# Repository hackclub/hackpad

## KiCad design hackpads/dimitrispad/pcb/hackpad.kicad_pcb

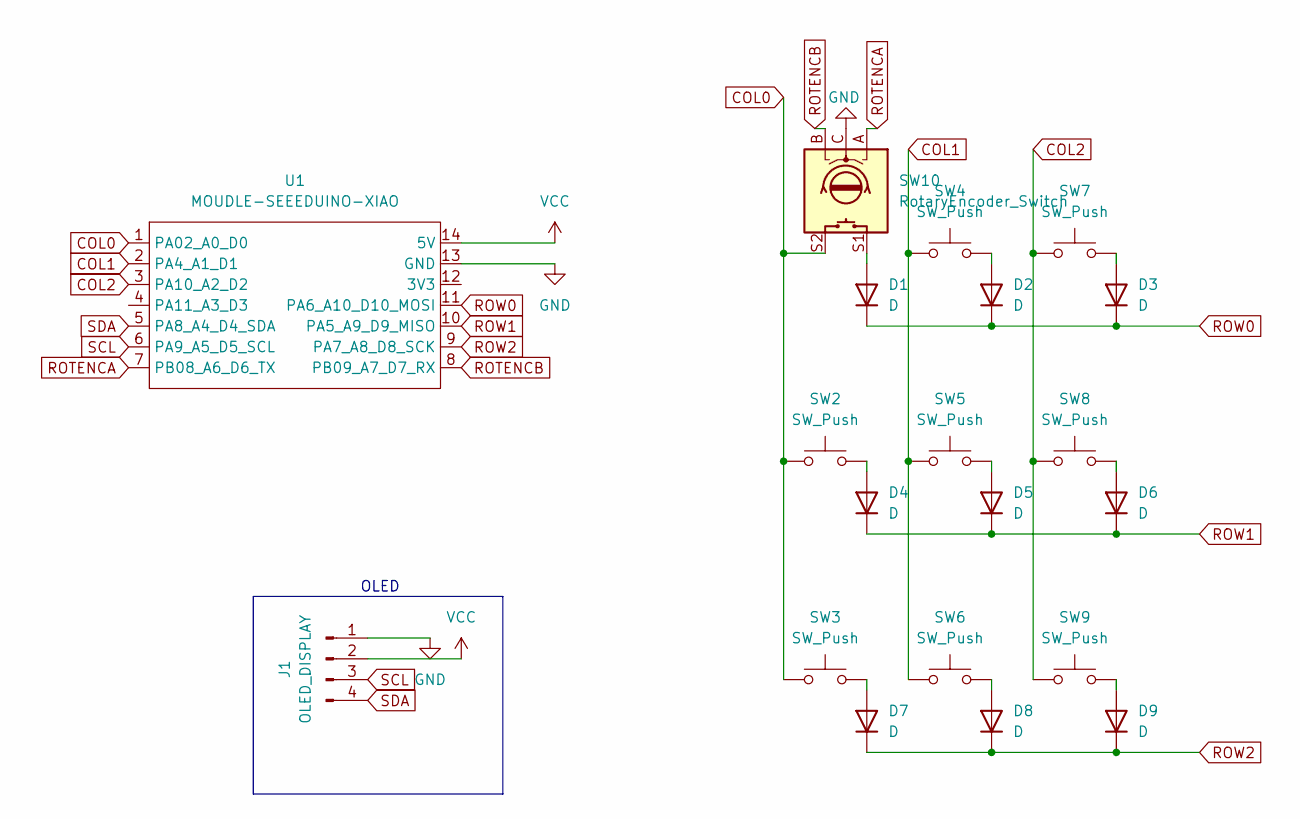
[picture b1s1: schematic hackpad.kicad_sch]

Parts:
D1, D2, D3, D4, D5, D6, D7, D8, D9: D; D_DO-35_SOD27_P7.62mm_Horizontal
J1: OLED_DISPLAY; SSD1306-0.91-OLED-4pin-128x32
SW2, SW3, SW4, SW5, SW6, SW7, SW8, SW9: SW_Push; SW_Cherry_MX_1.00u_PCB
SW10: RotaryEncoder_Switch; RotaryEncoder_Alps_EC11E-Switch_Vertical_H20mm
U1: MOUDLE-SEEEDUINO-XIAO; XIAO-Generic-Hybrid-14P-2.54-21X17.8MM

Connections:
COL0: SW2.1, SW3.1, SW10.S2, U1.1 (PA02_A0_D0)
COL1: SW4.1, SW5.1, SW6.1, U1.2 (PA4_A1_D1)
COL2: SW7.1, SW8.1, SW9.1, U1.3 (PA10_A2_D2)
GND: J1.1, SW10.C, U1.13 (GND)
unnamed: D1.2 (A), SW10.S1
unnamed: D2.2 (A), SW4.2
unnamed: D3.2 (A), SW7.2
unnamed: D4.2 (A), SW2.2
unnamed: D5.2 (A), SW5.2
unnamed: D6.2 (A), SW8.2
unnamed: D7.2 (A), SW3.2
unnamed: D8.2 (A), SW6.2
unnamed: D9.2 (A), SW9.2
ROTENCA: SW10.A, U1.7 (PB08_A6_D6_TX)
ROTENCB: SW10.B, U1.8 (PB09_A7_D7_RX)
ROW0: D1.1 (K), D2.1 (K), D3.1 (K), U1.11 (PA6_A10_D10_MOSI)
ROW1: D4.1 (K), D5.1 (K), D6.1 (K), U1.10 (PA5_A9_D9_MISO)
ROW2: D7.1 (K), D8.1 (K), D9.1 (K), U1.9 (PA7_A8_D8_SCK)
SCL: J1.3, U1.6 (PA9_A5_D5_SCL)
SDA: J1.4, U1.5 (PA8_A4_D4_SDA)
VCC: J1.2, U1.14 (5V)

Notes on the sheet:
OLED

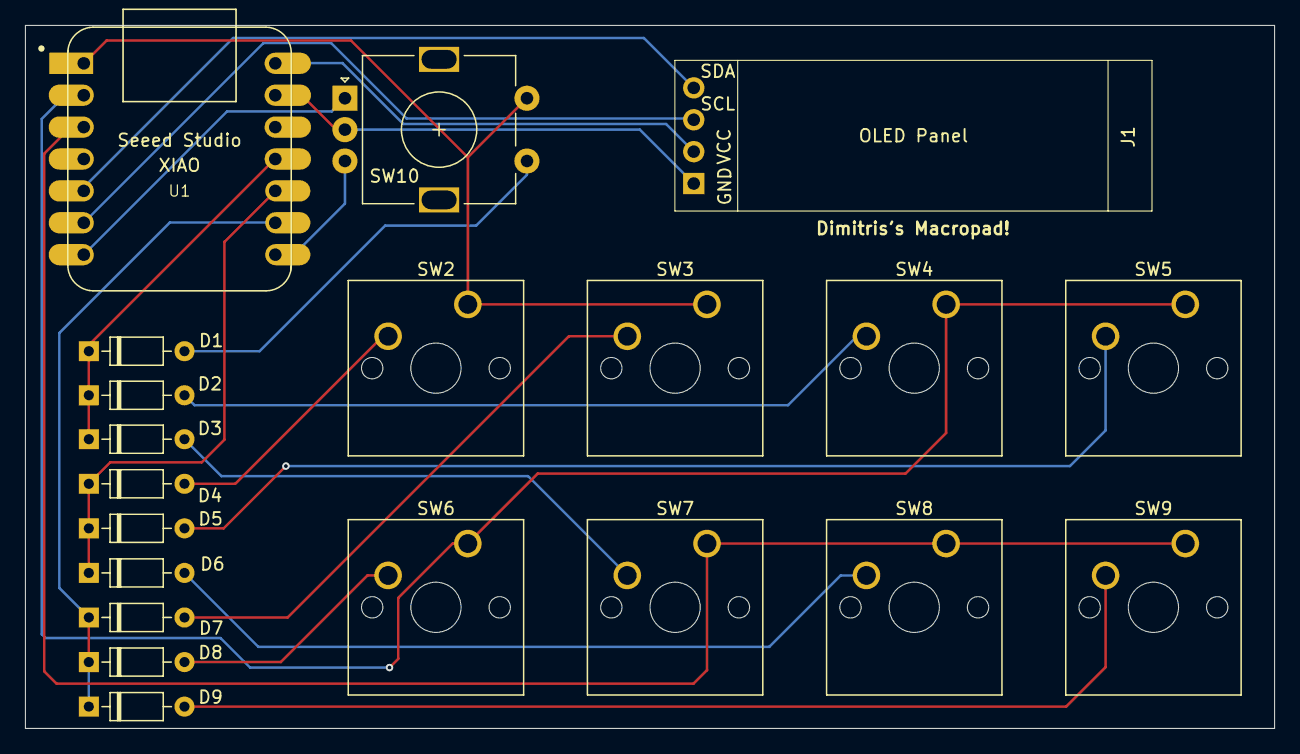
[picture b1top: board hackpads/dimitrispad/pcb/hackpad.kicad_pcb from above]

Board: 2 copper layers, 99.5 x 56.0 mm, 20 parts (0 on the bottom side), 21 nets.

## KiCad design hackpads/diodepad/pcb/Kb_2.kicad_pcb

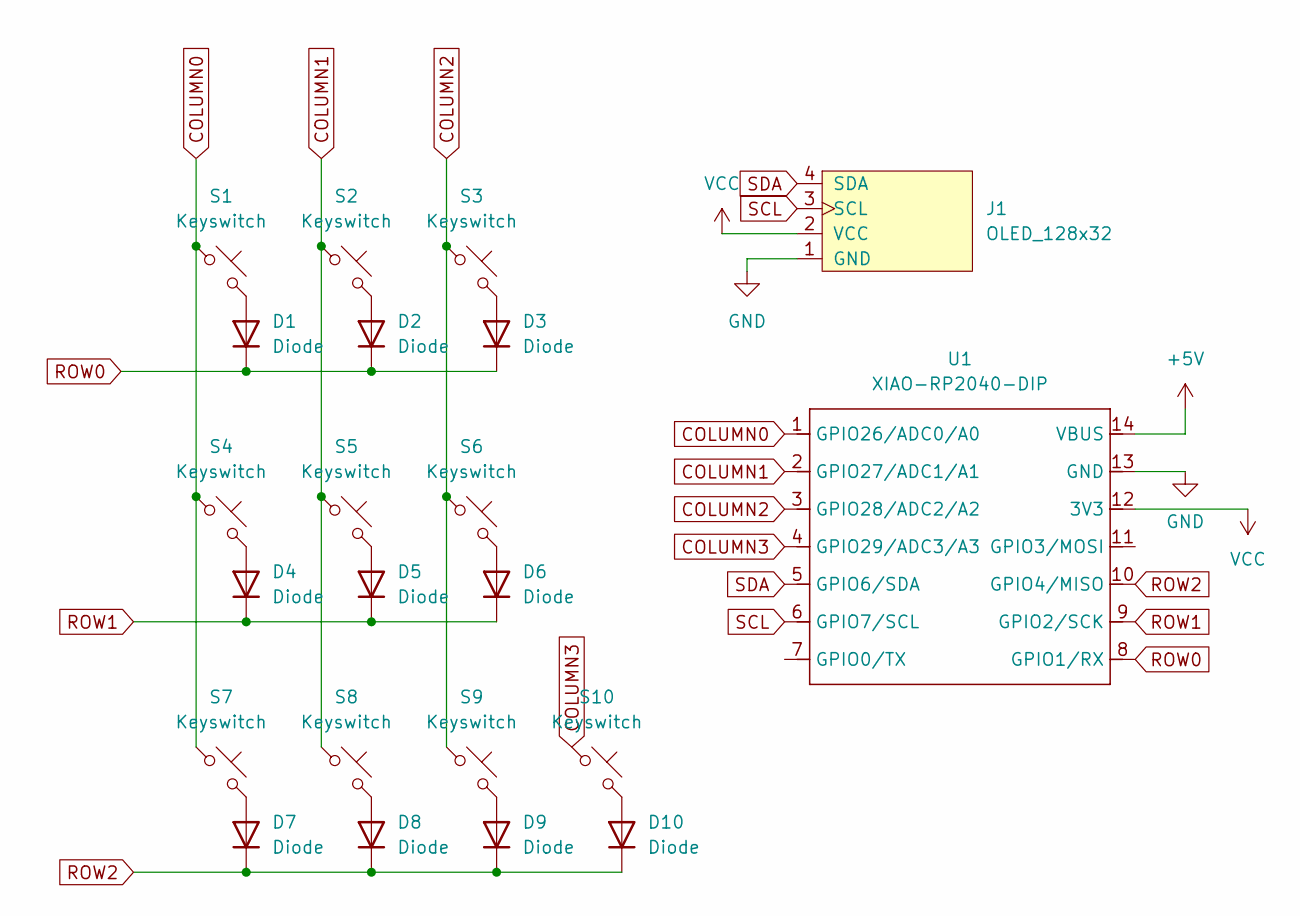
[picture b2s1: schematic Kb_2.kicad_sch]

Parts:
D1, D2, D3, D4, D5, D6, D7, D8, D9, D10: Diode; Diode_DO-35
J1: OLED_128x32
S1, S2, S3, S4, S5, S6, S7, S8, S9, S10: Keyswitch; MX_PCB_1.00u
U1: XIAO-RP2040-DIP

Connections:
+5V: U1.14 (VBUS)
COLUMN0: S1.1, S4.1, S7.1, U1.1 (GPIO26/ADC0/A0)
COLUMN1: S2.1, S5.1, S8.1, U1.2 (GPIO27/ADC1/A1)
COLUMN2: S3.1, S6.1, S9.1, U1.3 (GPIO28/ADC2/A2)
COLUMN3: S10.1, U1.4 (GPIO29/ADC3/A3)
GND: J1.1 (GND), U1.13 (GND)
unnamed: D1.2 (A), S1.2
unnamed: D2.2 (A), S2.2
unnamed: D3.2 (A), S3.2
unnamed: D4.2 (A), S4.2
unnamed: D5.2 (A), S5.2
unnamed: D6.2 (A), S6.2
unnamed: D7.2 (A), S7.2
unnamed: D8.2 (A), S8.2
unnamed: D9.2 (A), S9.2
unnamed: D10.2 (A), S10.2
ROW0: D1.1 (K), D2.1 (K), D3.1 (K), U1.8 (GPIO1/RX)
ROW1: D4.1 (K), D5.1 (K), D6.1 (K), U1.9 (GPIO2/SCK)
ROW2: D7.1 (K), D8.1 (K), D9.1 (K), D10.1 (K), U1.10 (GPIO4/MISO)
SCL: J1.3 (SCL), U1.6 (GPIO7/SCL)
SDA: J1.4 (SDA), U1.5 (GPIO6/SDA)
VCC: J1.2 (VCC), U1.12 (3V3)

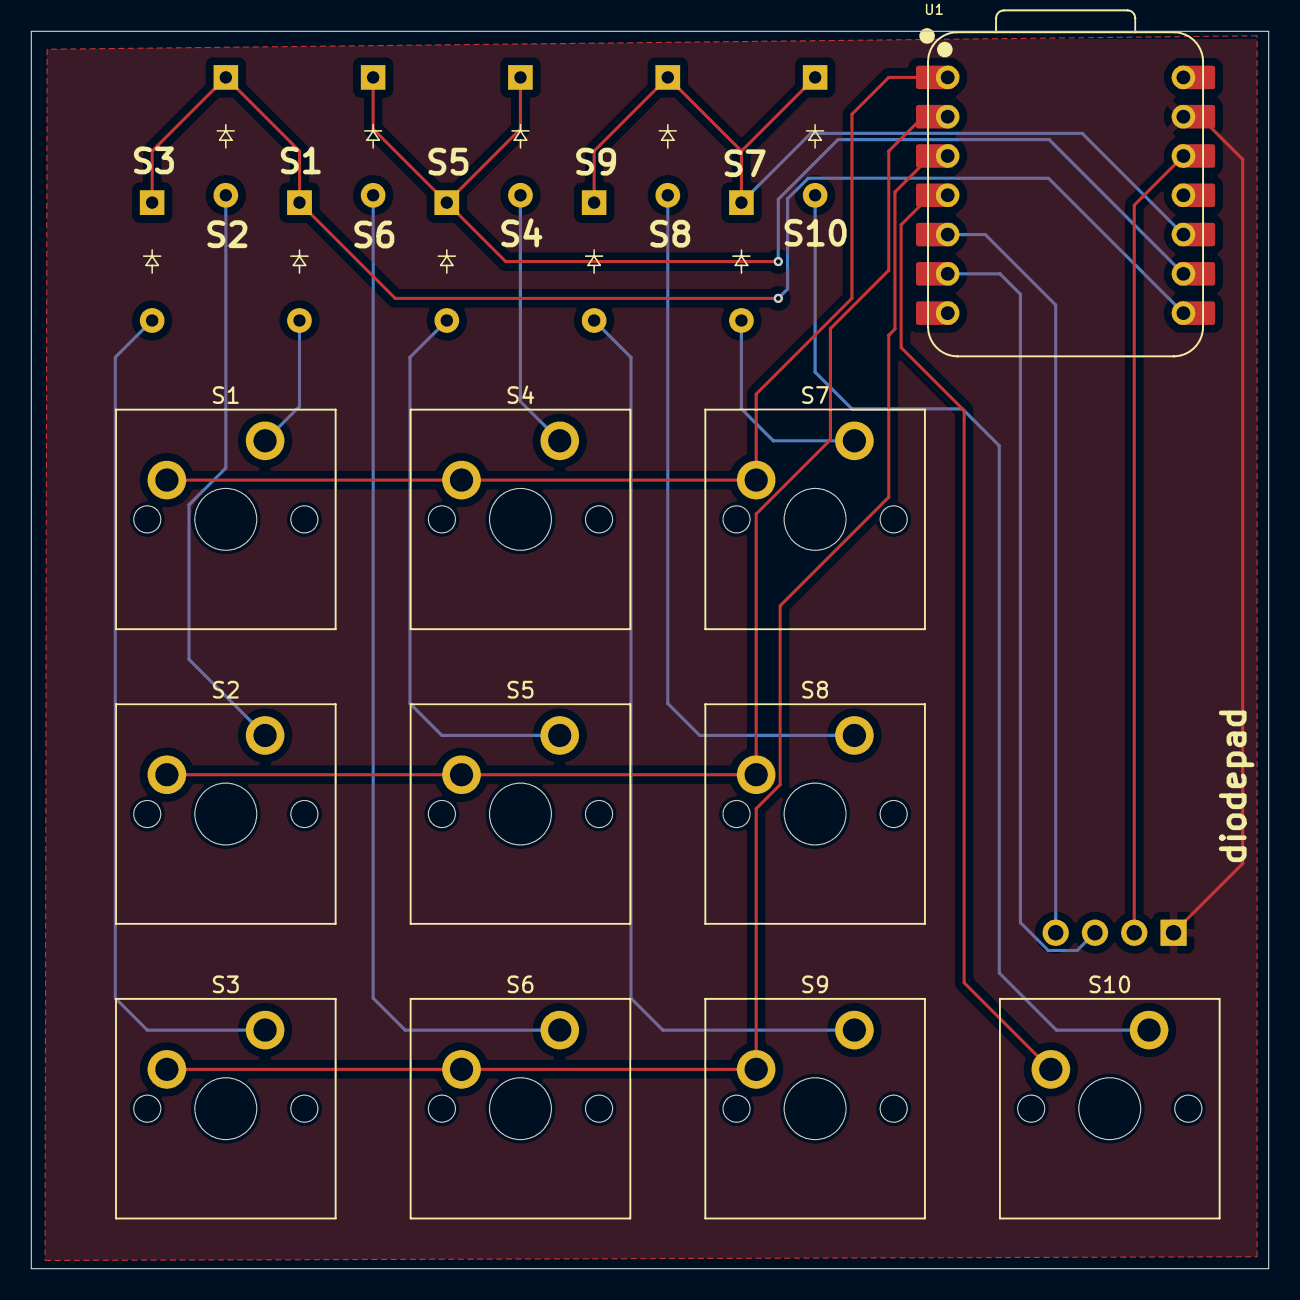
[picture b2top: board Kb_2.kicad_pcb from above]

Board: 2 copper layers, 80.0 x 80.0 mm, 22 parts (0 on the bottom side), 21 nets.

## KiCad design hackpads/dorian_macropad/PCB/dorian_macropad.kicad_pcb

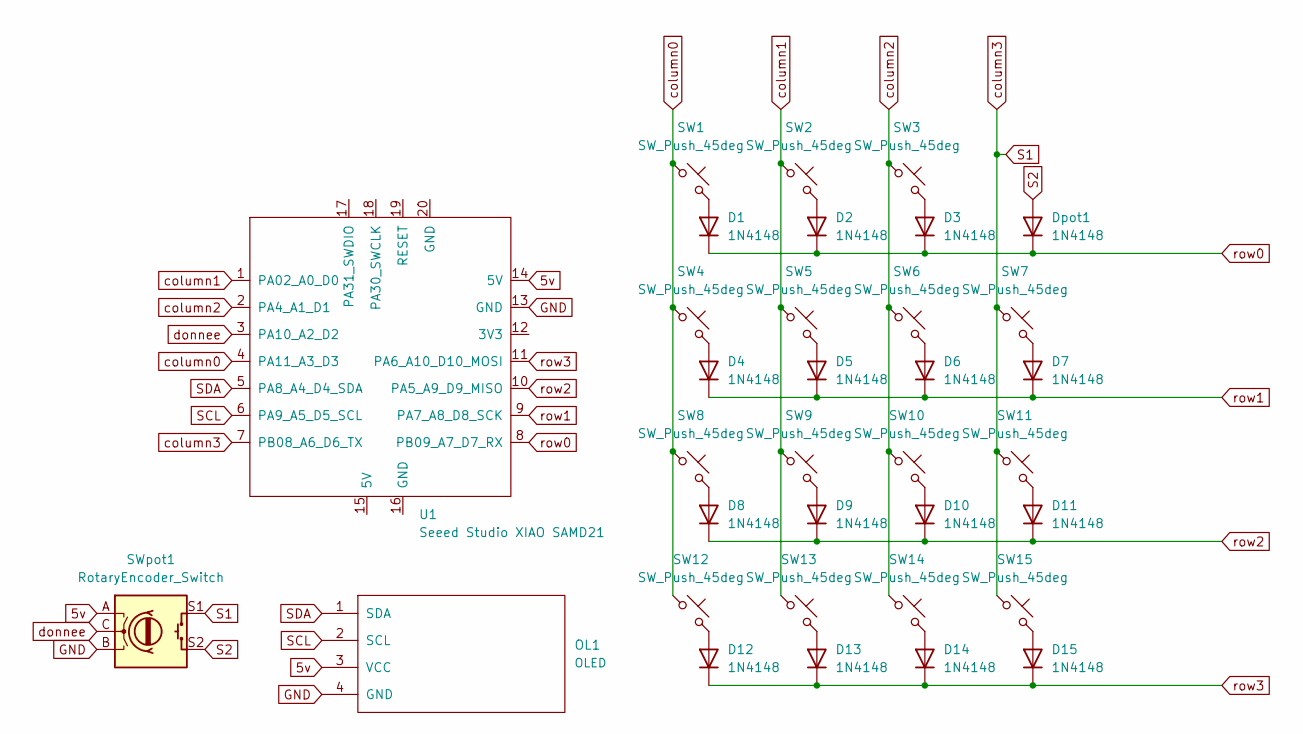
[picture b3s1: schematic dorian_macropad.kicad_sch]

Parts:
D1, D2, D3, D4, D5, D6, D7, D8, D9, D10, D11, D12, D13, D14, D15: 1N4148; D_DO-35_SOD27_P7.62mm_Horizontal
Dpot1: 1N4148; D_DO-35_SOD27_P7.62mm_Horizontal
OL1: OLED; 128x64OLED
SW1, SW2, SW3, SW4, SW5, SW6, SW7, SW8, SW9, SW10, SW11, SW12, SW13, SW14, SW15: SW_Push_45deg; SW_Cherry_MX_1.00u_PCB
SWpot1: RotaryEncoder_Switch; RotaryEncoder_Alps_EC11E-Switch_Vertical_H20mm
U1: Seeed Studio XIAO SAMD21; XIAO-SAMD21-DIP

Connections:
5v: OL1.3 (VCC), SWpot1.A, U1.14 (5V)
GND: OL1.4 (GND), SWpot1.B, U1.13 (GND)
unnamed: D1.2 (A), SW1.2
unnamed: D2.2 (A), SW2.2
unnamed: D3.2 (A), SW3.2
unnamed: D4.2 (A), SW4.2
unnamed: D5.2 (A), SW5.2
unnamed: D6.2 (A), SW6.2
unnamed: D7.2 (A), SW7.2
unnamed: D8.2 (A), SW8.2
unnamed: D9.2 (A), SW9.2
unnamed: D10.2 (A), SW10.2
unnamed: D11.2 (A), SW11.2
unnamed: D12.2 (A), SW12.2
unnamed: D13.2 (A), SW13.2
unnamed: D14.2 (A), SW14.2
unnamed: D15.2 (A), SW15.2
S1: SW7.1, SW11.1, SW15.1, SWpot1.S1, U1.7 (PB08_A6_D6_TX)
S2: Dpot1.2 (A), SWpot1.S2
SCL: OL1.2 (SCL), U1.6 (PA9_A5_D5_SCL)
SDA: OL1.1 (SDA), U1.5 (PA8_A4_D4_SDA)
column0: SW1.1, SW4.1, SW8.1, SW12.1, U1.4 (PA11_A3_D3)
column1: SW2.1, SW5.1, SW9.1, SW13.1, U1.1 (PA02_A0_D0)
column2: SW3.1, SW6.1, SW10.1, SW14.1, U1.2 (PA4_A1_D1)
donnee: SWpot1.C, U1.3 (PA10_A2_D2)
row0: D1.1 (K), D2.1 (K), D3.1 (K), Dpot1.1 (K), U1.8 (PB09_A7_D7_RX)
row1: D4.1 (K), D5.1 (K), D6.1 (K), D7.1 (K), U1.9 (PA7_A8_D8_SCK)
row2: D8.1 (K), D9.1 (K), D10.1 (K), D11.1 (K), U1.10 (PA5_A9_D9_MISO)
row3: D12.1 (K), D13.1 (K), D14.1 (K), D15.1 (K), U1.11 (PA6_A10_D10_MOSI)

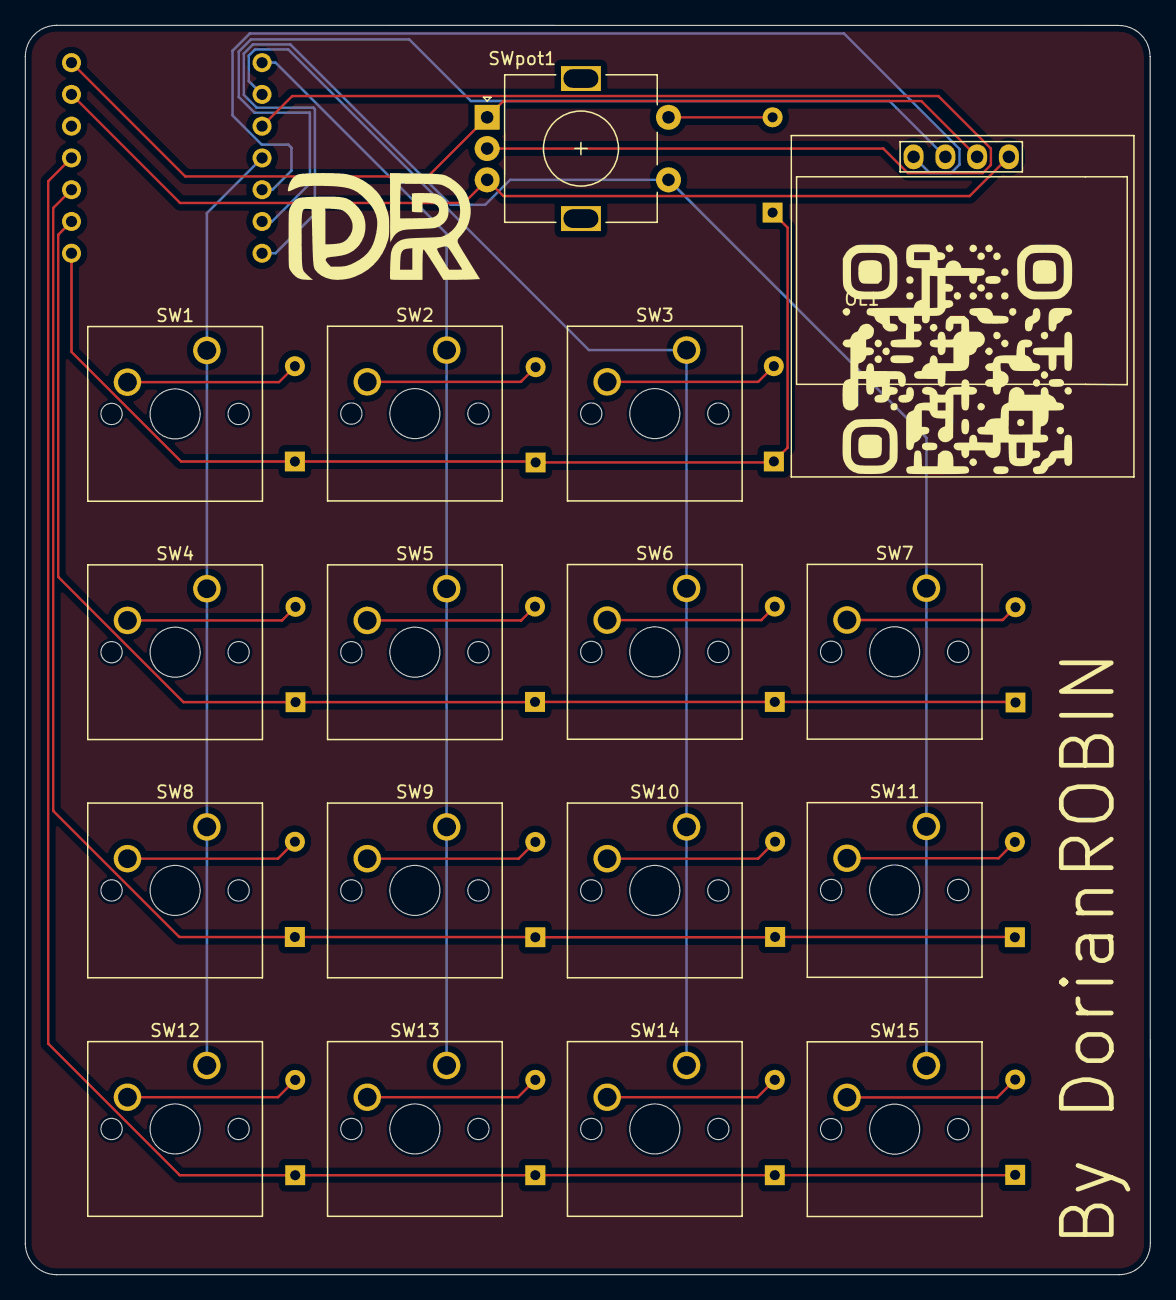
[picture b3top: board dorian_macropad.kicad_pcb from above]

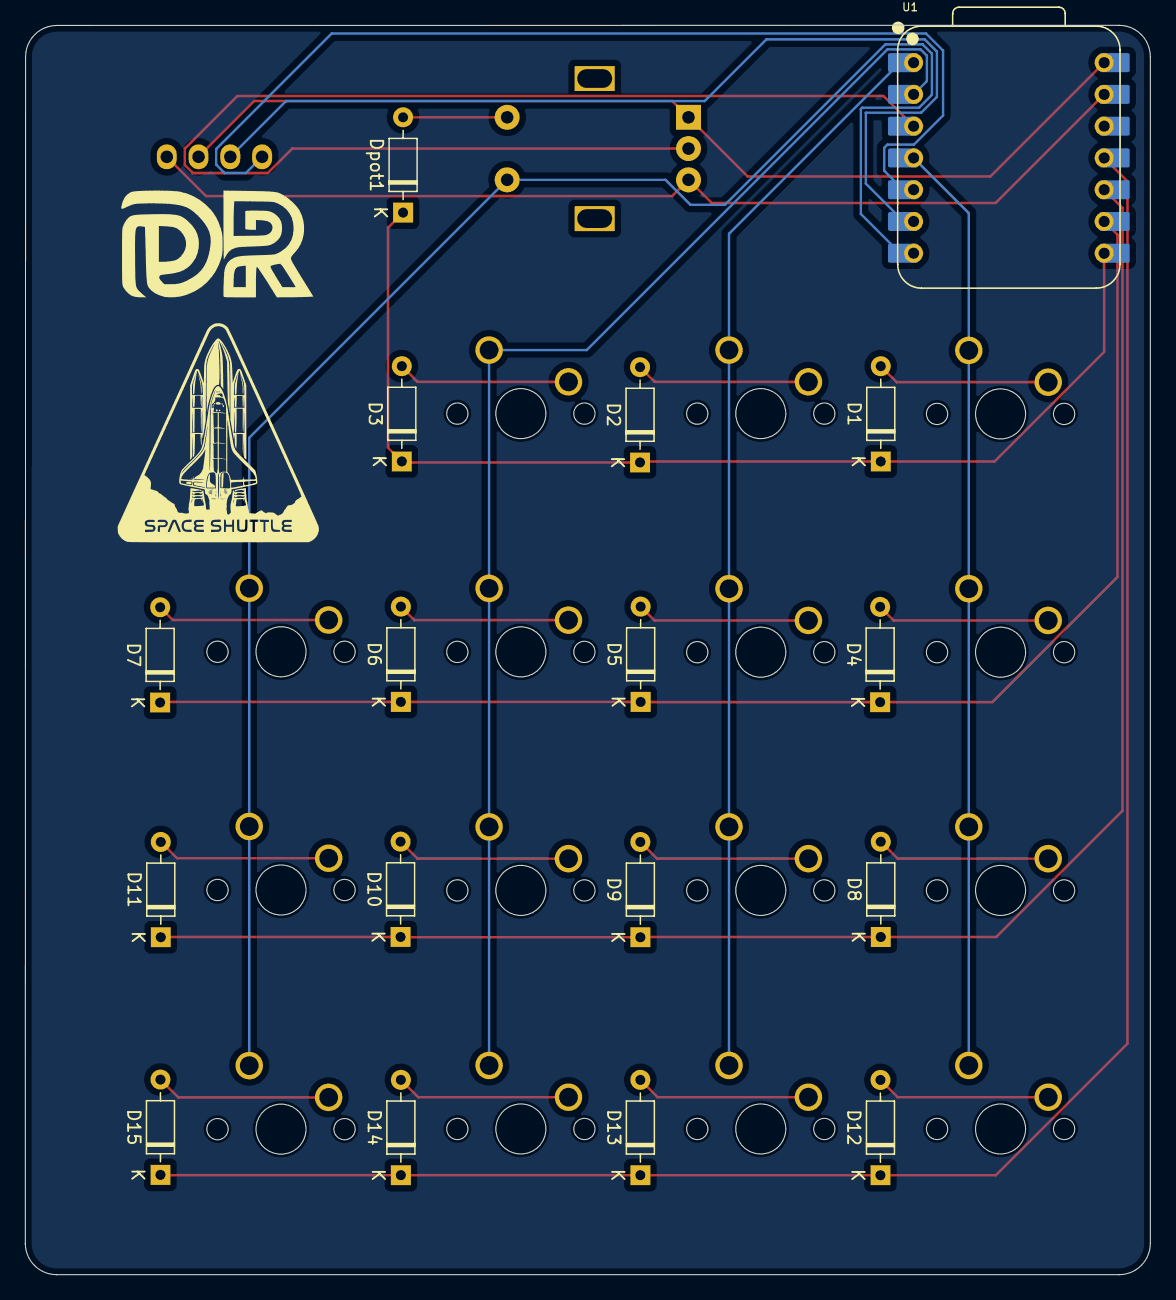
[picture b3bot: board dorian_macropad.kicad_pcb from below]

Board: 2 copper layers, 90.0 x 99.9 mm, 34 parts (17 on the bottom side), 29 nets.

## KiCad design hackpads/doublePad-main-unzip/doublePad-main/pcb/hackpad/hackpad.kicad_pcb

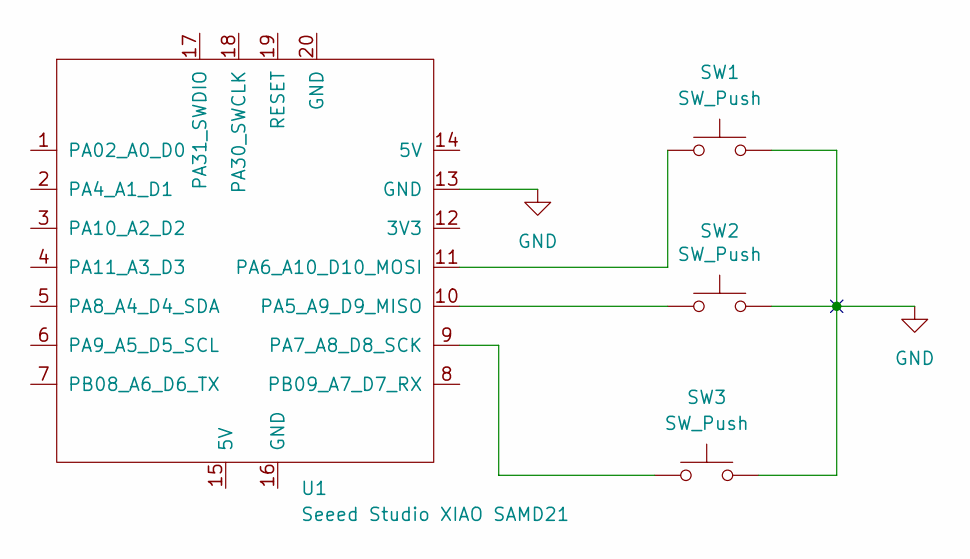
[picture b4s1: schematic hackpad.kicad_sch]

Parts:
SW1, SW2, SW3: SW_Push; SW_Cherry_MX_1.00u_PCB
U1: Seeed Studio XIAO SAMD21; XIAO-Generic-Thruhole-14P-2.54-21X17.8MM

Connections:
GND: SW1.2, SW2.2, SW3.2, U1.13 (GND)
unnamed: SW2.1, U1.10 (PA5_A9_D9_MISO)
unnamed: SW1.1, U1.11 (PA6_A10_D10_MOSI)
unnamed: SW3.1, U1.9 (PA7_A8_D8_SCK)

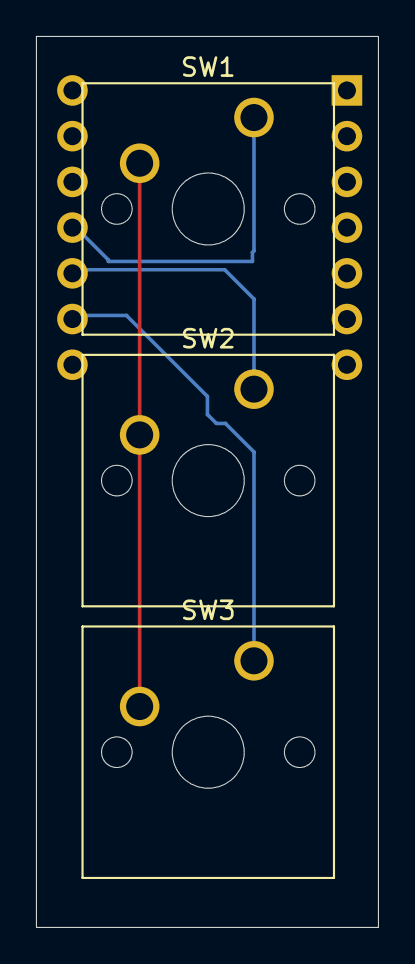
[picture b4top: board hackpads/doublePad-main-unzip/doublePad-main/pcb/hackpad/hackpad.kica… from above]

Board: 2 copper layers, 19.0 x 49.5 mm, 4 parts (1 on the bottom side), 4 nets.

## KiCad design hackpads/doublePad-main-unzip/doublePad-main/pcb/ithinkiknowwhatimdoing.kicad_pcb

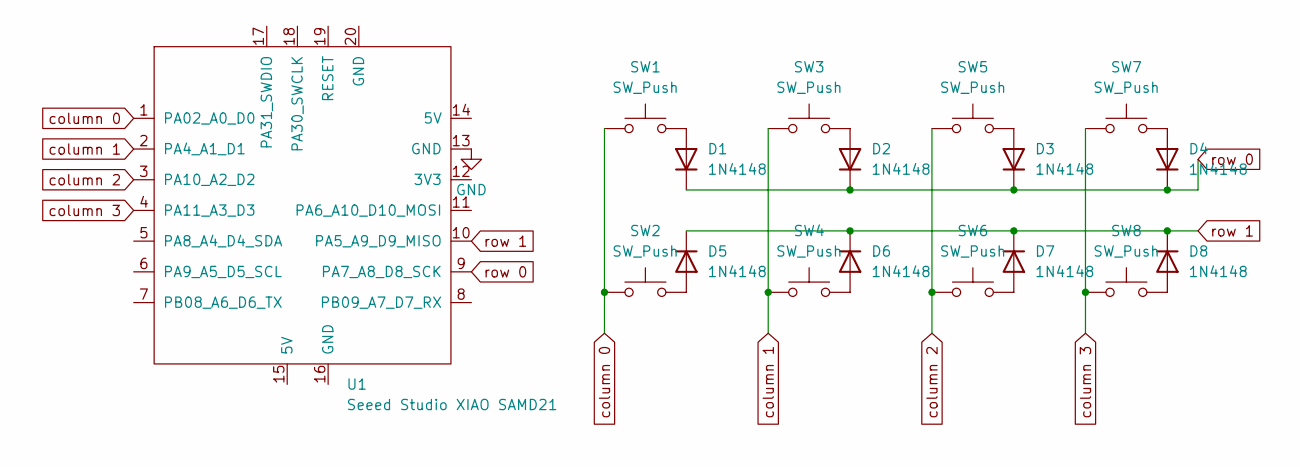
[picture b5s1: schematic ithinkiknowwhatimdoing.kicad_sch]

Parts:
D1, D2, D3, D4, D5, D6, D7, D8: 1N4148; D_DO-35_SOD27_P7.62mm_Horizontal
SW1, SW2, SW3, SW4, SW5, SW6, SW7, SW8: SW_Push; SW_Cherry_MX_1.00u_Plate
U1: Seeed Studio XIAO SAMD21; XIAO-Generic-Thruhole-14P-2.54-21X17.8MM

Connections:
GND: U1.13 (GND)
unnamed: D1.2 (A), SW1.2
unnamed: D2.2 (A), SW3.2
unnamed: D3.2 (A), SW5.2
unnamed: D4.2 (A), SW7.2
unnamed: D5.2 (A), SW2.2
unnamed: D6.2 (A), SW4.2
unnamed: D7.2 (A), SW6.2
unnamed: D8.2 (A), SW8.2
column 0: SW1.1, SW2.1, U1.1 (PA02_A0_D0)
column 1: SW3.1, SW4.1, U1.2 (PA4_A1_D1)
column 2: SW5.1, SW6.1, U1.3 (PA10_A2_D2)
column 3: SW7.1, SW8.1, U1.4 (PA11_A3_D3)
row 0: D1.1 (K), D2.1 (K), D3.1 (K), D4.1 (K), U1.9 (PA7_A8_D8_SCK)
row 1: D5.1 (K), D6.1 (K), D7.1 (K), D8.1 (K), U1.10 (PA5_A9_D9_MISO)

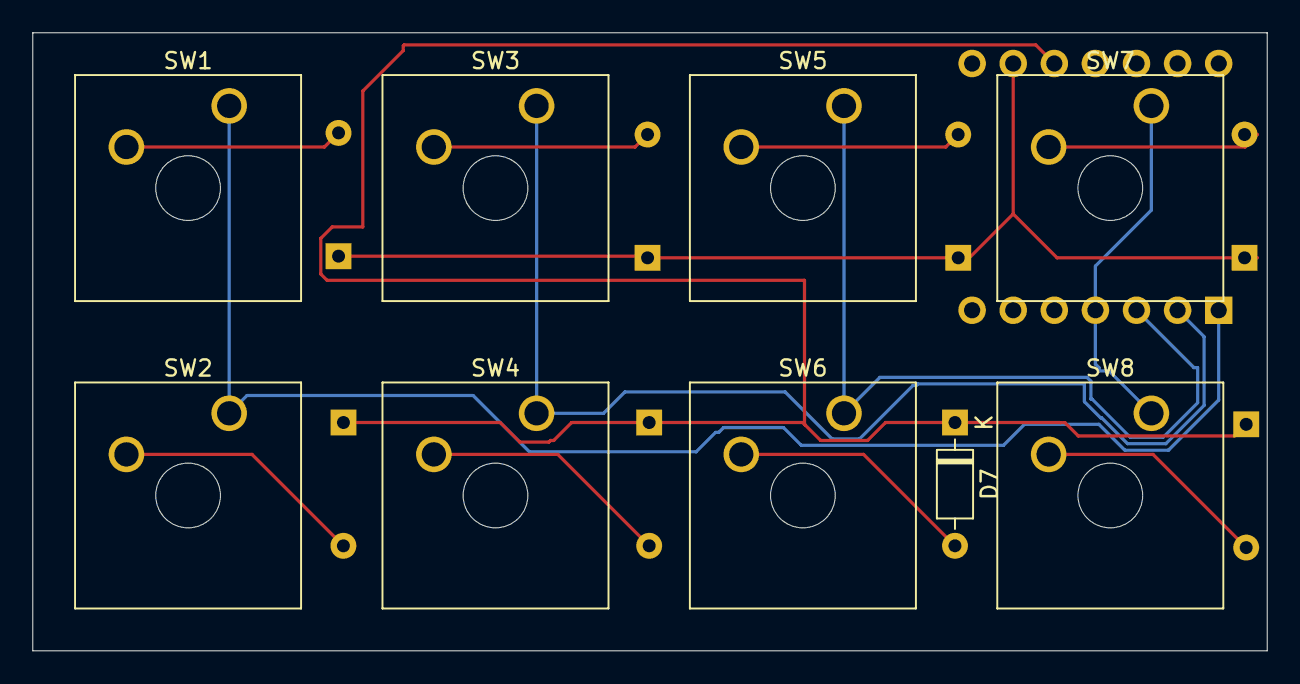
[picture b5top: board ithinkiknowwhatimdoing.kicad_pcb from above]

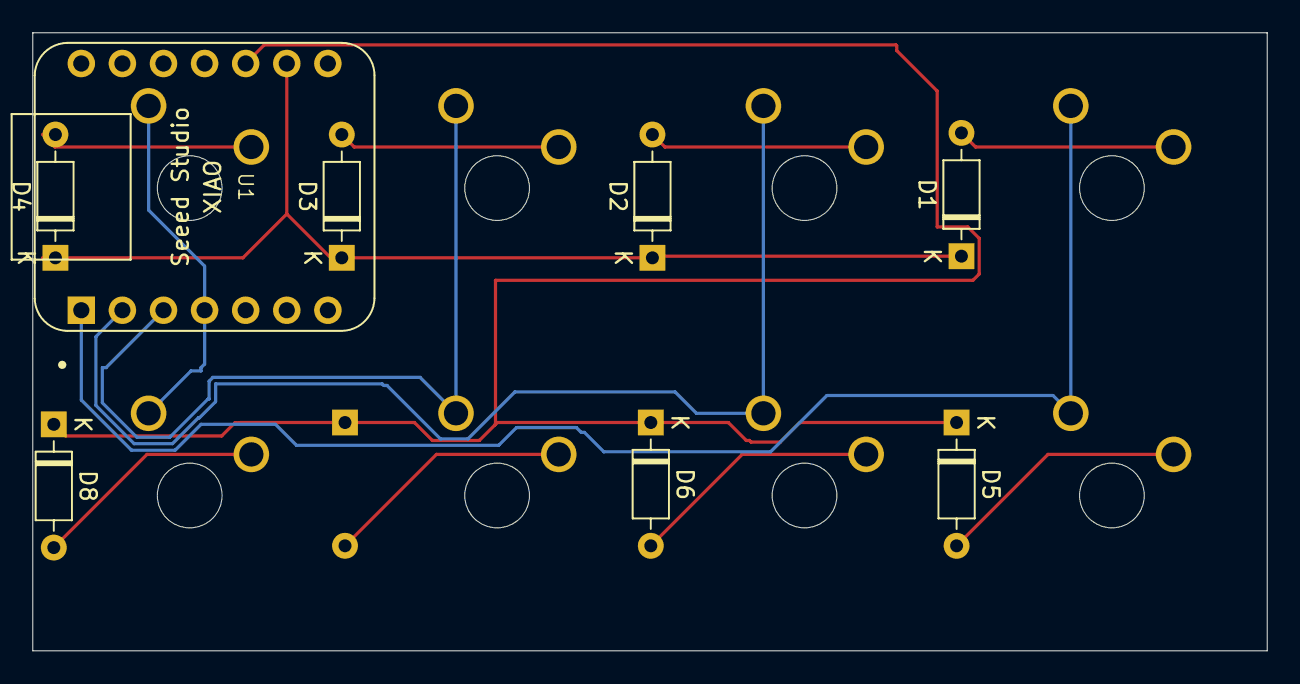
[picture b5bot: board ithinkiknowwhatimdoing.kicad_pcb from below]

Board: 2 copper layers, 76.3 x 38.2 mm, 17 parts (8 on the bottom side), 14 nets.
